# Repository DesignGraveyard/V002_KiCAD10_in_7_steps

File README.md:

# Description

Master KiCad 10 in just 7 steps! In this video tutorial, I will show you how to design your own PCB in KiCAD10.  
I will use a  ESP32-S3 USB development board from a previous video as example and guide you through the design process in 7 steps:  

* **Step 1:** Schematic Design & Workspace Setup
* **Step 2:** Component Selection & Footprint Assignment
* **Step 3:** Creating Custom Schematic Symbol (USB PCB Connector)
* **Step 4:** Designing Custom PCB Footprints
* **Step 5:** PCB Outline & Component Placement
* **Step 6:** Track Routing & Ground Copper Fills
* **Step 7:** Design Rule Check (DRC) & Exporting Gerbers  

Finally we will order, build & test the PCB. 

You can order the PCB Directly at PCBWay:  

### Watch the YouTube video, it will guide you through the process step by step:  

### Link to the GitHub with assembly instructions:  https://github.com/DesignGraveyard/V001_ESP32_bad_USB
For good contact the USB connector thickness is 2mm to 2.2mm, please check the instruction video and GitHub for the ESP32 "Bad USB" for more information.
### Download KiCAD10 here: www.kicad.org and ...please make a donation to the KiCAD team!

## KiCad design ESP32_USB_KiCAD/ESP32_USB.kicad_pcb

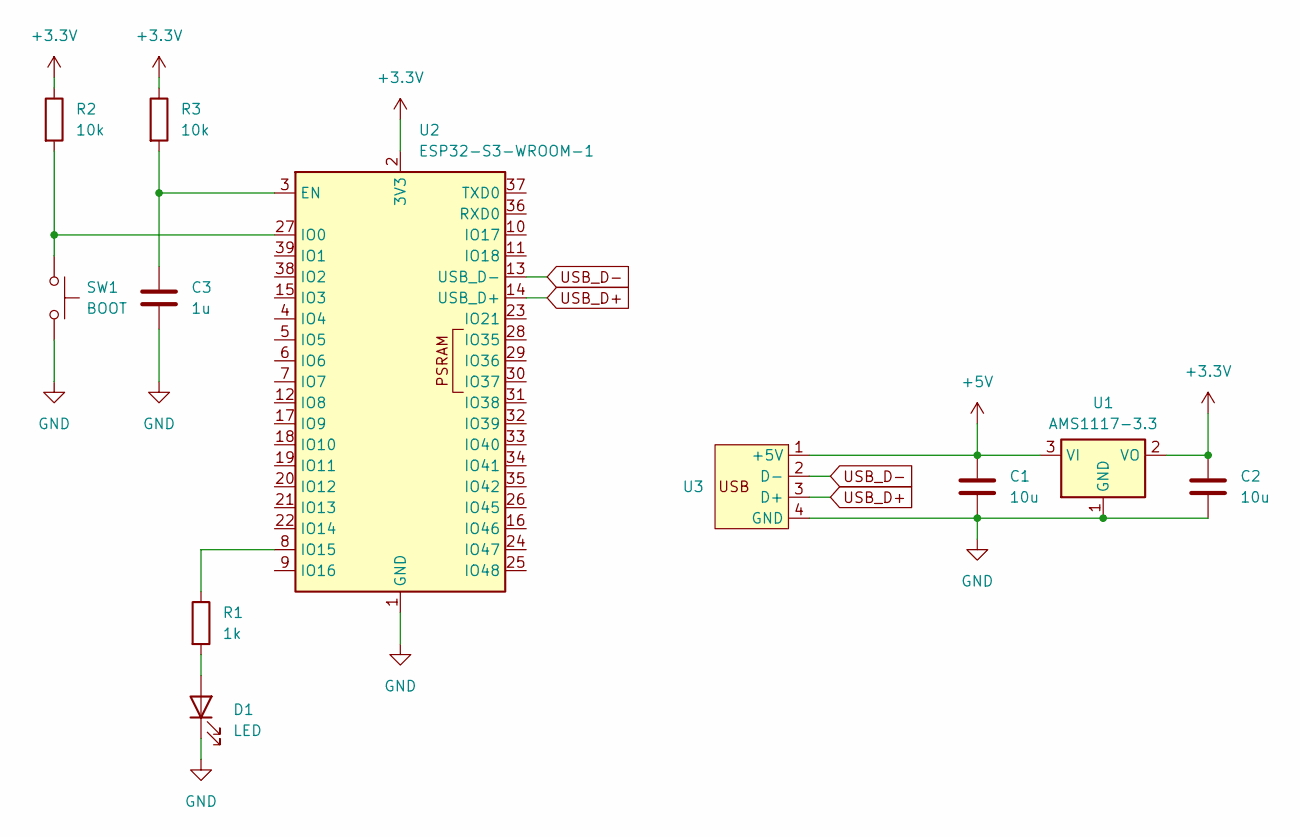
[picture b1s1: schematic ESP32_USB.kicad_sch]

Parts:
C1, C2: 10u; C_0805_2012Metric_Pad1.18x1.45mm_HandSolder
C3: 1u; C_0805_2012Metric_Pad1.18x1.45mm_HandSolder
D1: LED; LED_0805_2012Metric_Pad1.15x1.40mm_HandSolder
R1: 1k; R_0805_2012Metric_Pad1.20x1.40mm_HandSolder
R2, R3: 10k; R_0805_2012Metric_Pad1.20x1.40mm_HandSolder
SW1: BOOT; SW_Tactile_SPST_NO_Straight_CK_PTS636Sx25SMTRLFS
U1: AMS1117-3.3; SOT-223-3_TabPin2
U2: ESP32-S3-WROOM-1
U3: USB_PCB_connector

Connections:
+3.3V: C2.1, R2.1, R3.1, U1.2 (VO), U2.2 (3V3)
+5V: C1.1, U1.3 (VI), U3.1 (+5V)
GND: C1.2, C2.2, C3.2, D1.1 (K), SW1.2, U1.1 (GND), U2.1 (GND), U2.40 (GND), U2.41 (GND), U3.4 (GND)
unnamed: D1.2 (A), R1.2
unnamed: C3.1, R3.2, U2.3 (EN)
unnamed: R2.2, SW1.1, U2.27 (IO0)
unnamed: R1.1, U2.8 (IO15)
USB_D+: U2.14 (USB_D+), U3.3 (D+)
USB_D-: U2.13 (USB_D-), U3.2 (D-)

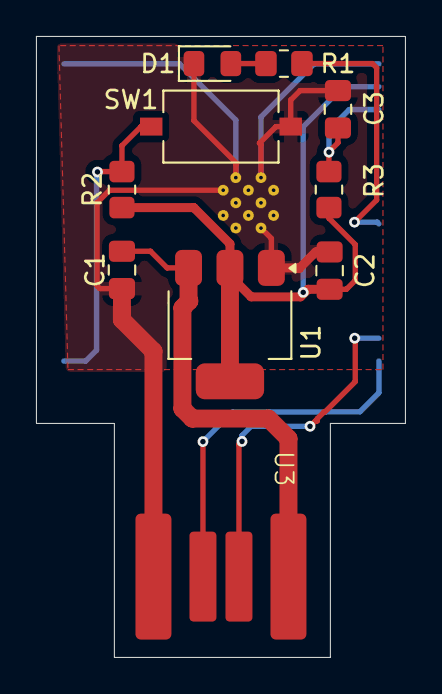
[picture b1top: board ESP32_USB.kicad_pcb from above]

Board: 2 copper layers, 20.5 x 34.5 mm, 11 parts (1 on the bottom side), 9 nets.

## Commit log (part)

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2026-06-02 README.md
